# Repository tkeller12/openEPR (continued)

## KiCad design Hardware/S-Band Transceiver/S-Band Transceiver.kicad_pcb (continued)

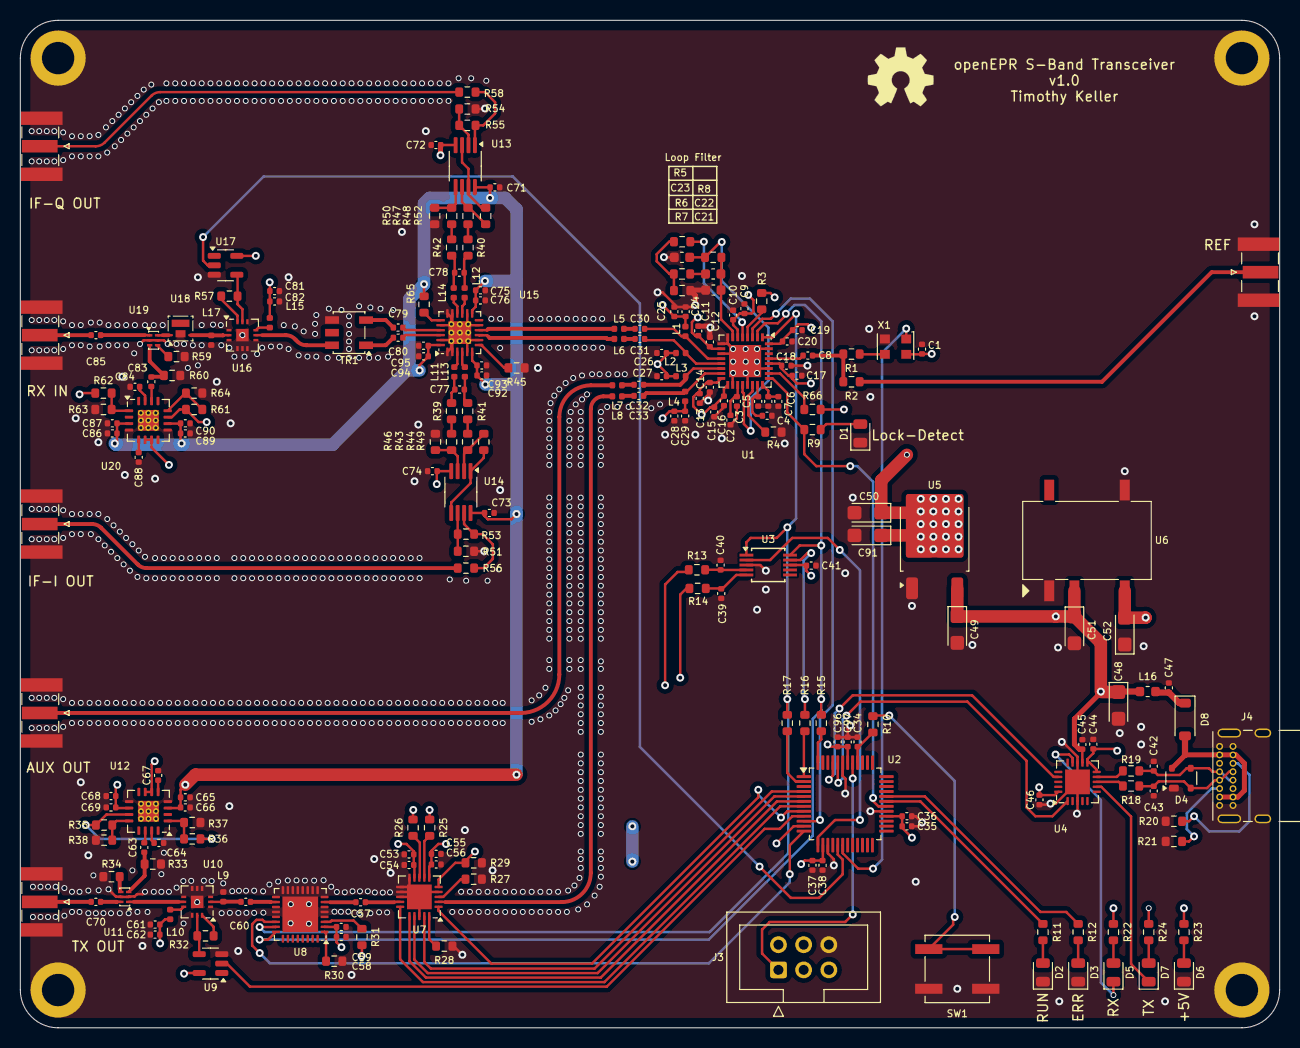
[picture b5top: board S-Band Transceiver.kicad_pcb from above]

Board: 4 copper layers, 127.0 x 101.6 mm, 223 parts (0 on the bottom side), 148 nets.

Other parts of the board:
C91: 10uF; CP_EIA-3216-18_Kemet-A

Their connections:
+3.3VA: C91.1; also elsewhere on the board
GND: C91.2; also elsewhere on the board

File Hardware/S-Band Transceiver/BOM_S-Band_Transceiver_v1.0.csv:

"Reference","Value","Footprint","Qty","DNP","Digikey"
"C1,C2,C4,C6,C9,C11,C13,C15,C17,C19,C25,C28,C34,C35,C37,C41,C44,C45,C46,C47,C53,C55,C58,C61,C65,C67,C68,C71,C72,C73,C74,C75,C81,C86,C88,C89,C92,C94,C96","100nF","Capacitor_SMD:C_0402_1005Metric","39","",""
"C3,C5,C7,C10,C12,C14,C16,C18,C20,C62,C82","10pF","Capacitor_SMD:C_0402_1005Metric","11","",""
"C8,C36,C38,C39,C40,C97","10nF","Capacitor_SMD:C_0402_1005Metric","6","",""
"C21","2.7nF","Capacitor_SMD:C_0603_1608Metric","1","",""
"C22","47nF","Capacitor_SMD:C_0603_1608Metric","1","",""
"C23","680pF","Capacitor_SMD:C_0603_1608Metric","1","",""
"C24,C26,C27,C29","120pF","Capacitor_SMD:C_0402_1005Metric","4","",""
"C30,C31,C32,C33","1nF","Capacitor_SMD:C_0402_1005Metric","4","",""
"C42,C43","47pF","Capacitor_SMD:C_0402_1005Metric","2","",""
"C48,C49,C50,C52,C91","10uF","Capacitor_Tantalum_SMD:CP_EIA-3216-18_Kemet-A","5","",""
"C51","4.7uF","Capacitor_Tantalum_SMD:CP_EIA-3216-18_Kemet-A","1","",""
"C54,C56,C59,C66,C69,C76,C87,C90,C93,C95","100pF","Capacitor_SMD:C_0402_1005Metric","10","",""
"C57,C60,C63,C64,C70,C79,C80,C83,C84,C85","10000pF","Capacitor_SMD:C_0402_1005Metric","10","","1284-1540-1-ND"
"C77,C78","3pF","Capacitor_SMD:C_0402_1005Metric","2","DNP",""
"D1,D2,D5,D6,D7","150080VS75000","LED_SMD:LED_0805_2012Metric","5","",""
"D3","150080SS75000","LED_SMD:LED_0805_2012Metric","1","",""
"D4","SP0503BAHTG","Package_TO_SOT_SMD:SOT-143","1","","F2715CT-ND"
"D8","1N5819","Diode_SMD:D_SOD-123","1","",""
"H1,H2,H3,H4","4-40","B12T_MountingHole:4-40_Hole_Pad","4","",""
"J1,J2,J5,J6,J7,J8","SMA-J-P-H-ST-EM1","Connector_Coaxial:SMA_Samtec_SMA-J-P-X-ST-EM1_EdgeMount","6","","SAM8857-ND"
"J3","AVR-UPDI-6","Connector_IDC:IDC-Header_2x03_P2.54mm_Vertical","1","",""
"J4","USB_C_Receptacle_USB2.0_16P","Connector_USB:USB_C_Receptacle_GCT_USB4085","1","","2073-USB4085-GF-ACT-ND"
"L1,L2,L3,L4","7.5nH","Inductor_SMD:L_0402_1005Metric","4","",""
"L5,L6,L7,L8","1.9nH","Inductor_SMD:L_0402_1005Metric","4","",""
"L9,L10,L15,L17","100nH","Inductor_SMD:L_0402_1005Metric","4","",""
"L11,L12,L13,L14","200nH","Inductor_SMD:L_0402_1005Metric","4","",""
"L16","MH1608-601Y","Inductor_SMD:L_0603_1608Metric","1","",""
"R1,R2,R7,R39,R40,R41,R42,R56,R58","0","Resistor_SMD:R_0603_1608Metric","9","",""
"R3,R25,R26,R27,R28,R29,R30,R31,R45,R66","10k","Resistor_SMD:R_0603_1608Metric","10","",""
"R4","4.7k","Resistor_SMD:R_0603_1608Metric","1","",""
"R5","0","Resistor_SMD:R_0603_1608Metric","1","DNP",""
"R6","360","Resistor_SMD:R_0603_1608Metric","1","",""
"R8,R9,R10,R11,R12,R13,R14,R22,R23,R24","1k","Resistor_SMD:R_0603_1608Metric","10","",""
"R15,R16,R17,R18,R19","27","Resistor_SMD:R_0603_1608Metric","5","",""
"R20,R21","5.1k","Resistor_SMD:R_0603_1608Metric","2","",""
"R32,R57","3.92k","Resistor_SMD:R_0603_1608Metric","2","",""
"R33,R60","60.4","Resistor_SMD:R_0603_1608Metric","2","",""
"R34,R59","50","Resistor_SMD:R_0603_1608Metric","2","",""
"R35,R61","3.74","Resistor_SMD:R_0603_1608Metric","2","",""
"R36,R62,R65","1.5k","Resistor_SMD:R_0603_1608Metric","3","",""
"R37,R63","270","Resistor_SMD:R_0603_1608Metric","2","",""
"R38,R64","2k","Resistor_SMD:R_0603_1608Metric","2","",""
"R43,R44,R47,R48,R51,R54","200","Resistor_SMD:R_0603_1608Metric","6","",""
"R46,R49,R50,R52,R53,R55","430","Resistor_SMD:R_0603_1608Metric","6","",""
"SW1","SW_Push","Button_Switch_SMD:SW_SPST_B3SL-1002P","1","",""
"TR1","ETC1-1-13","Transformer_SMD:Transformer_MACOM_SM-22","1","","1465-1217-1-ND"
"U1","ADF4351","Package_CSP:LFCSP-32-1EP_5x5mm_P0.5mm_EP3.25x3.25mm","1","","505-ADF4351BCPZ-RL7CT-ND"
"U2","AVR128DA48x-xPT","Package_QFP:TQFP-48_7x7mm_P0.5mm","1","","150-AVR128DA48-I/PT-ND"
"U3","ADS1118IDGS","Package_SO:MSOP-10_3x3mm_P0.5mm","1","","296-38850-1-ND"
"U4","FT231XQ","Package_DFN_QFN:QFN-20-1EP_4x4mm_P0.5mm_EP2.5x2.5mm","1","","768-1128-1-ND"
"U5","AZ1117ID-3.3TRG1","Package_TO_SOT_SMD:TO-252-2","1","","AZ1117ID-3.3TRG1-ND"
"U6","IES0105S05-H","_tim-DC-DC:IES0105S05-H","1","","1470-IES0105S05-H-ND"
"U7","DAT-31A+","Package_DFN_QFN:QFN-20-1EP_4x4mm_P0.5mm_EP2.5x2.5mm","1","","3157-DAT-31A-PP+CT-ND"
"U8","PE44820","Package_DFN_QFN:QFN-32-1EP_5x5mm_P0.5mm_EP3.6x3.6mm","1","","1046-1144-1-ND"
"U9,U17","SN74LVC1G125DCK","Package_TO_SOT_SMD:SOT-23-5","2","","296-11604-1-ND"
"U10,U16","TSS-53LNB3+","_tim-RF-Mini-Circuits:DQ1225","2","","3157-TSS-53LNB3+CT-ND"
"U11,U19","DCW-22-332+","_tim-RF-Mini-Circuits:JC0603C","2","","3157-DCW-22-332+CT-ND"
"U12,U20","ADL5906","Package_DFN_QFN:QFN-16-1EP_4x4mm_P0.65mm_EP2.1x2.1mm_ThermalVias","2","","505-ADL5906ACPZN-R7CT-ND"
"U13,U14","LT1819","Package_SO:MSOP-8_3x3mm_P0.65mm","2","","LT1819CS8#TRPBFCT-ND"
"U15","ADL5380","Package_CSP:LFCSP-24-1EP_4x4mm_P0.5mm_EP2.3x2.3mm_ThermalVias","1","","505-ADL5380ACPZ-R7CT-ND"
"U18","SKY16603-632LF","_tim-RF:DFN-2-2.3x2.3","1","","863-SKY16603-632LFCT-ND"
"X1","XO32","Oscillator:Oscillator_SMD_EuroQuartz_XO32-4Pin_3.2x2.5mm","1","",""

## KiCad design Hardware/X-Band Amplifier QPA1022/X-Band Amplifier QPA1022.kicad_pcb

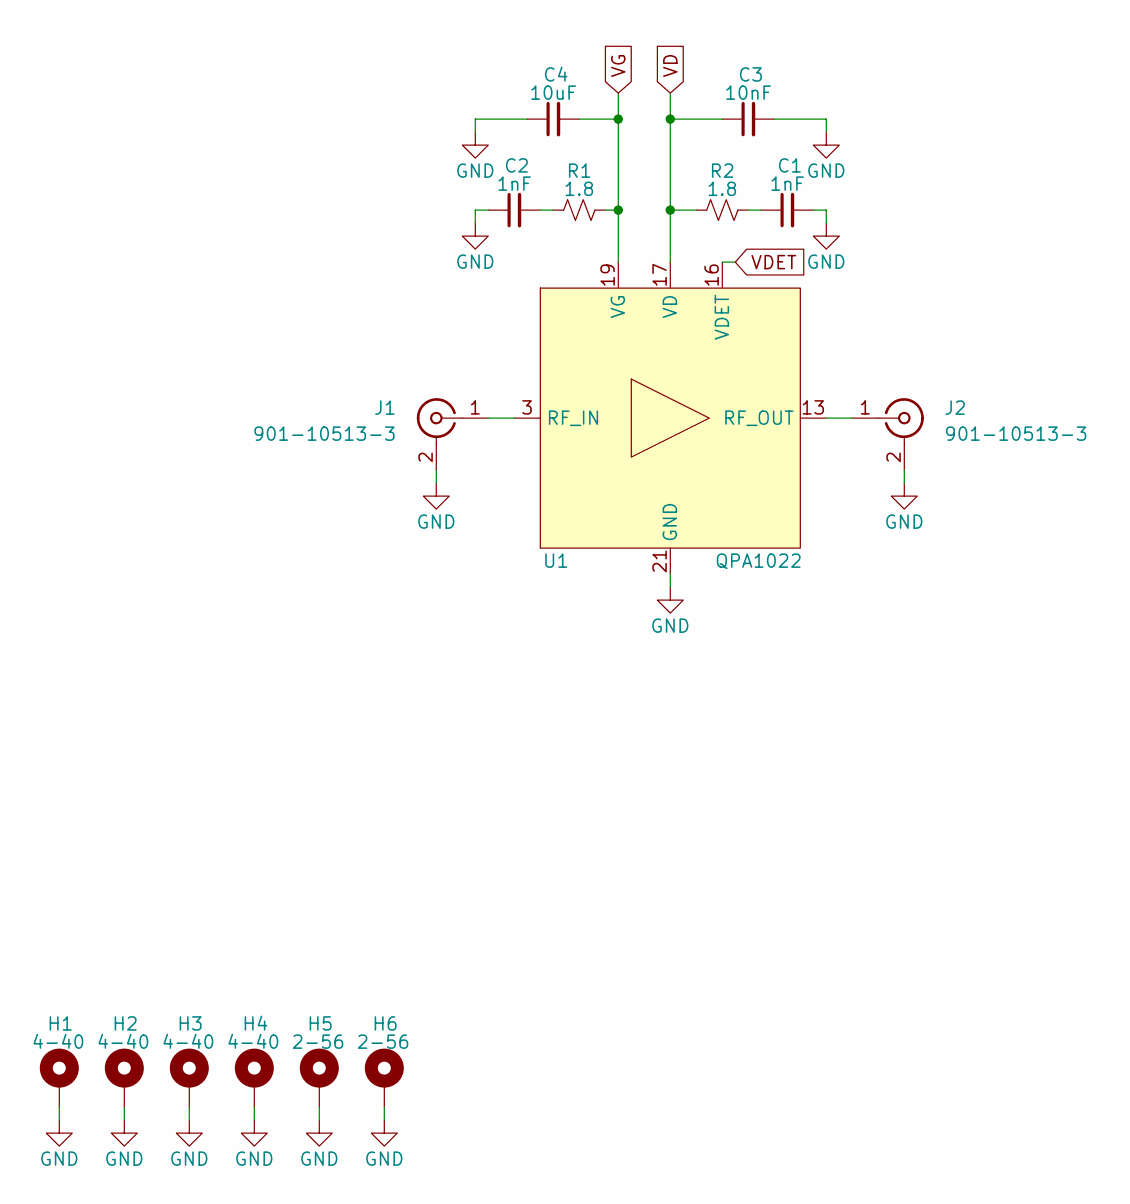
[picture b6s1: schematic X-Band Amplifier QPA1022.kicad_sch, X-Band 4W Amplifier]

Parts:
C1, C2: 1nF; C_0402_1005Metric
C3: 10nF; C_0402_1005Metric
C4: 10uF; C_0402_1005Metric
H1, H2, H3, H4: 4-40; 4-40_Hole_Pad
H5, H6: 2-56; 2-56_Hole_Pad
J1, J2: 901-10513-3; AMPHENOL_901-10513-3_EDGE_LAUNCH_Female
R1, R2: 1.8; R_0402_1005Metric
U1: QPA1022; QFN-20-1EP_4x4mm_P0.5mm_EP2.5x2.5mm_ThermalVias

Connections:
GND: C1.2, C2.1, C3.2, C4.1, H1.1, H2.1, H3.1, H4.1, H5.1, H6.1, J1.2 (Ext), J2.2 (Ext), U1.1 (NC), U1.2 (NC), U1.4 (NC), U1.5 (NC), U1.6 (NC), U1.7 (NC), U1.8 (NC), U1.9 (NC), U1.10 (NC), U1.11 (NC), U1.12 (NC), U1.14 (NC), U1.15 (NC), U1.18 (NC), U1.20 (NC), U1.21 (GND)
unnamed: C1.1, R2.2
unnamed: C2.2, R1.1
unnamed: J1.1 (In), U1.3 (RF_IN)
unnamed: J2.1 (In), U1.13 (RF_OUT)
VD: C3.1, R2.1, U1.17 (VD)
VDET: U1.16 (VDET)
VG: C4.2, R1.2, U1.19 (VG)

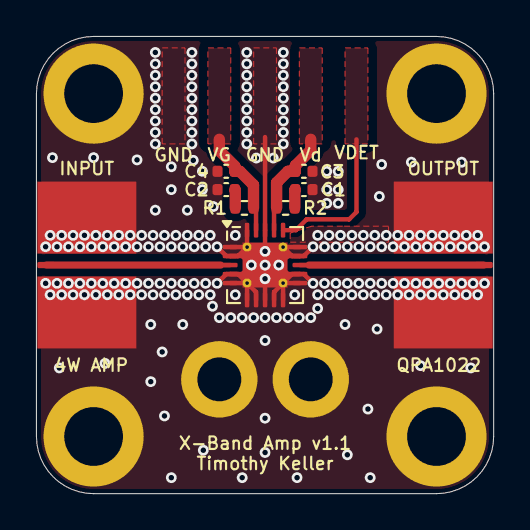
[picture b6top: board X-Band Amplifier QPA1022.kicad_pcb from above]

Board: 4 copper layers, 25.4 x 25.4 mm, 15 parts (0 on the bottom side), 7 nets.

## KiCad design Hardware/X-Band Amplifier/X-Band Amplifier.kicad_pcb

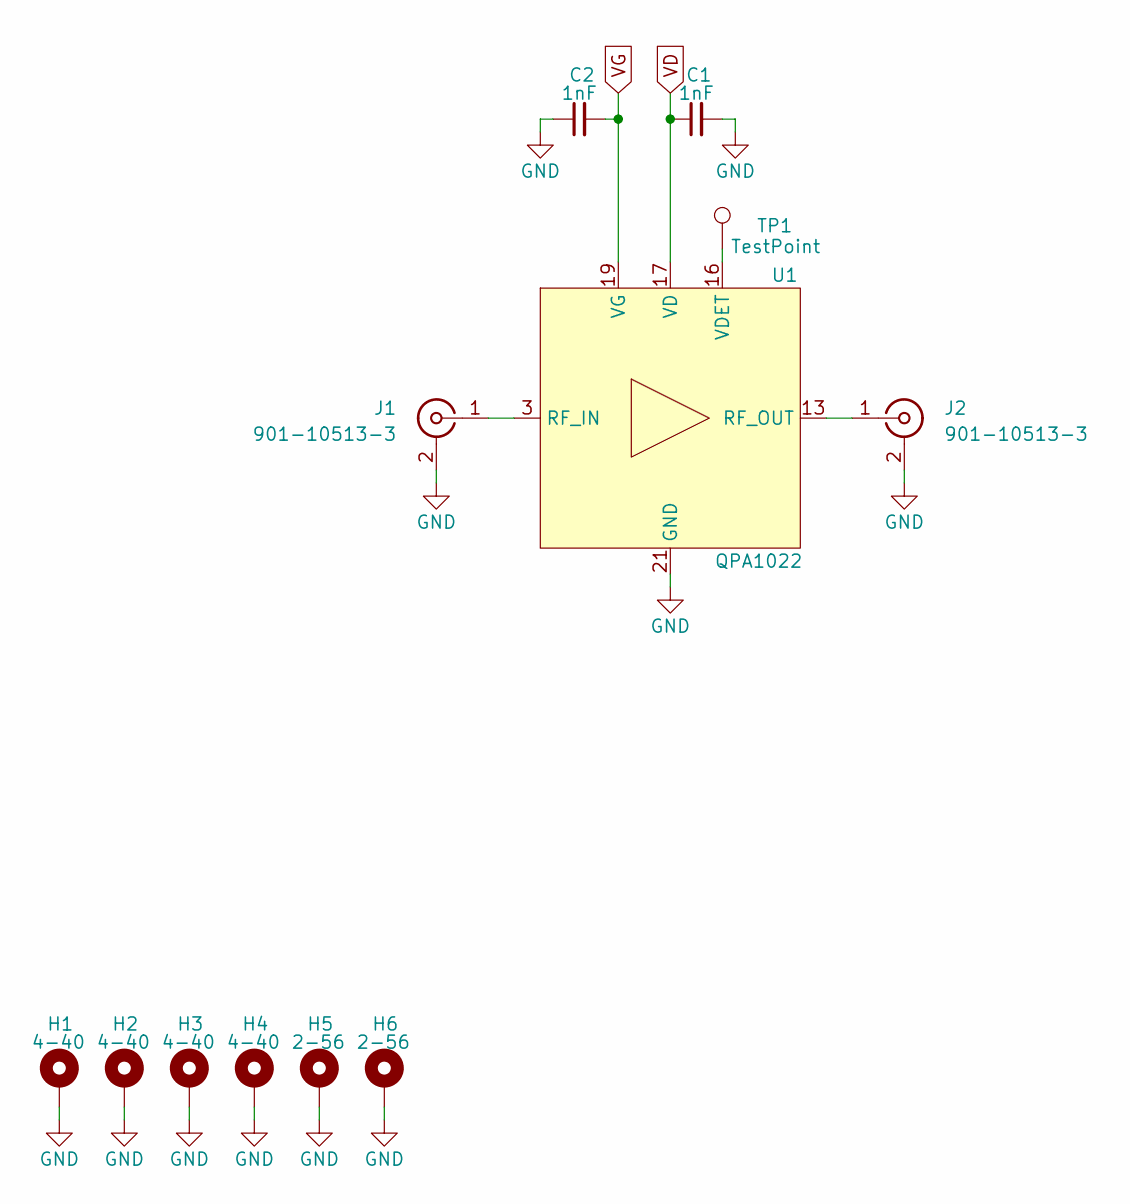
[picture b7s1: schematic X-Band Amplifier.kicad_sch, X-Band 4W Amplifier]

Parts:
C1, C2: 1nF; C_0402_1005Metric
H1, H2, H3, H4: 4-40; 4-40_Hole_Pad
H5, H6: 2-56; 2-56_Hole_Pad
J1, J2: 901-10513-3; AMPHENOL_901-10513-3_EDGE_LAUNCH_Female
TP1: TestPoint; TestPoint_Pad_D1.0mm
U1: QPA1022; QFN-20-1EP_4x4mm_P0.5mm_EP2.5x2.5mm_ThermalVias

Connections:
GND: C1.2, C2.1, H1.1, H2.1, H3.1, H4.1, H5.1, H6.1, J1.2 (Ext), J2.2 (Ext), U1.1 (NC), U1.2 (NC), U1.4 (NC), U1.5 (NC), U1.6 (NC), U1.7 (NC), U1.8 (NC), U1.9 (NC), U1.10 (NC), U1.11 (NC), U1.12 (NC), U1.14 (NC), U1.15 (NC), U1.18 (NC), U1.20 (NC), U1.21 (GND)
unnamed: J1.1 (In), U1.3 (RF_IN)
unnamed: J2.1 (In), U1.13 (RF_OUT)
unnamed: TP1.1, U1.16 (VDET)
VD: C1.1, U1.17 (VD)
VG: C2.2, U1.19 (VG)

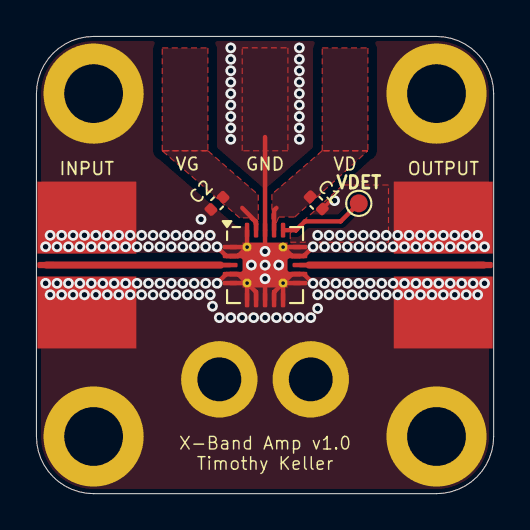
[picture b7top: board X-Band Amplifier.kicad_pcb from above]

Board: 4 copper layers, 25.4 x 25.4 mm, 12 parts (0 on the bottom side), 6 nets.
